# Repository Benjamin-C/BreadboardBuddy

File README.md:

# Breadboard Buddy

An RP2040 microcontroller designed to fit neatly on the end of a breadboard

Important: Some software features listed here are not yet implemented. Run the `help` command to see the commands actually implemented in the current firmware version

# Specs
### Power
| Parameter      |     | Min | Typ | Max | Unit |
|----------------|-----|-----|-----|-----|------|
| Input Voltage  | USB |     | 5   |     | V    |
|                | EXT | 5   | 12  | 30  | V    |
|                | AIN | 0   |     | 3.3 | V    |
|                | GPIO| 0   |     | 3.3 | V    |
| Input Current  | USB |     |     | 0.5 | A    |
|                | EXT |     |     | 2   | A    |
|                | GPIO|     |     | 10  | mA   |
| Output Voltage | 3v3 |     | 3.3 |     | V    |
|                | 3v3A|     | 3.3 |     | V    |
|                | GPIO| 0   |     | 3.3 | V    |
| Output Current | 3v3 | 0.5 |     | 2   | A    |
|                | GPIO|     |     | 10  | mA   |

### System
* Microcontroller: RP2040
* Flash: 2MB

### Peripherals
* 16 GPIO pins capable of input with pull up/down and constant or PWM output.
* 4 analog inputs
* 1 LED connected to GPIO16
* 1 barrel jack switch connected to GPIO17
* 1 button connected to GPIO18

# Setup

## Wiring
Connect the Breadboard Buddy to a breadboard's power rails. Ensure that the positive and negative outputs go to the red and blue sides of each rail. Connect external circuitry to the GPIO or analog pins. If you are doing a lot of analog circuitry, you may with to configure the right rail to be disconnected and manually connect 3v3A there instead. If you are using any voltage higher than 3.3V in your circuit, ensure that it can not reach any of the input pins to the microcontroller.

Connect the USB port of the Breadboard Buddy to your computer, and open and connect your favorite serial monitor.

## Configuration

The right power rail can be configured to output 3v3, EXT, or USB by moving the jumper near the barrel jack. Removing this jumper disconnects that power rail.

Each pin that you want to be an output will have to be explicitly set up as such by using the `mode` command. GPIO pins can be set up as digital inputs or outputs, or PWM outputs. Analog pins can only be set up as analog inputs.

## Firmware
The Breadboard Buddy firmware runs on CircuitPython. To Install it:
1. Download CircuitPython for the Raspberry Pi Pico from https://circuitpython.org/board/raspberry_pi_pico/
2. Connect the Breadboard Buddy to your computer. Disconnect anything else from the Breadboard Buddy.
3. Press and hold the `Reset` button, then press and hold the `Boot` button
4. Release the `Reset` button then release the `Boot` button.
5. The Breadboard buddy should appear as a USB mass storage device named `RPI-RP2`. If this does not happen, try steps 3 and 4 again, waiting longer between actions. If the issue precisest, you have an issue with your hardware.
6. Copy CircuitPython file `adafruit-circuitpython-raspberry_pi_pico-en_US-<version>.uf2` onto the Breadboard Buddy. It should reboot when this is complete.
7. The Breadboard Buddy should now appear as a USB mass storage device named `CIRCUITPY`. If this does not happen, try again from step 3. If the issue precisest, you have an issue with your hardware.
8. Copy `code.py` from `firmware` onto the Breadboard Buddy. The Breadboard Buddy should blink its light several times. You have now installed the Breadboard Buddy firmware.

It is possible to run other software on the Breadboard Buddy either through CircuitPython or by flashing it yourself. This guide will not help you with that.

# Usage

The Breadboard Buddy is interfaced with by sending commands over serial and reading their response.

## Command Types
There are two forms of commands, questions and instructions.
### Instructions
An instruction tells the Breadboard Buddy to do something. This could be to change a configuration field, or set an output value. Most instructions will take the form `<instruction> <field> <value>`. If no value is provided, the command will be assumed to be a question.
### Questions
Questions are asked in the form `<question>[?] <field>`. While the question mark is not required, it is encouraged since any command given with a question mark will be interpreted as a question, even if values are given (in which case they will be ignored).

## Pins
### Pin Fields
For commands that take a pin as a field, there are several ways the pin can be specified. 
#### By number
Pins can be specified by number. Digital pins are 0-15. Analog pins are  ain0-ain4. Example: `5`, `12`, `3`, `ain2`
#### By Name
Pins can also be set up to be identified by a name. Names can be used in place of numbers. Names must be unique for each pin, and each pin can only have 1 alias. Names may contain letters and numbers, but no dashes, spaces, or other characters. Names must start with a letter. Names are not case sensitive, but the given case is stored. Example: `LED`, `BitClk`, `Q`, `Addr2`
#### By range
Pins can be specified by a range. Ranges are specified by a start pin then a dash then the end pin. Ranges are inclusive. The range will be evaluated in the order given. If names are used, they will be converted to pin numbers before the range is calculated. Names and numbers can be mixed. You may not mix analog and digital pins in a range. Example: `0-7`, `ADDR0-ADDR4`, `ain0-ain3`
#### By list
Pins can be specified by a list. Lists are comma separated. The command will execute on each pin in the order they are specified. Names and numbers can be mixed. Example: `1,2,8,4`, `ADDR0,ADDR1,ADDR2`

### Pin States

#### Digital
Digital pins can be either high, low, or a PWM value. When specifying the state of a pin, you can use

* `H`, `HIGH`, `1`, `ON` for high output
* `L`, `LOW`, `0`, `OFF` for low output
* Numbers from 0.000 to 1.000 (only if the pin is configured as PWM)

Note that `ON` and `OFF` should be avoided if you are using active low logic to avoid confusion since they do not reverse for active low signals.

#### Analog
Analog pins will return the voltage on that pin in the form `#.###`. Analog pins can not be set to values.

## Commands

Some commands have a short form and a long form. The short form is the part of the long form shown in CAPS. Either form is acceptable. No part of a command is case sensitive. Multiple fields are separated by spaces. Commands listed with a ? are read only. 

All commands are in the form `<command>[?] <pin(s)> [field(s)]`

| Command | Allowed Fields                         | Action
|---------|----------------------------------------|- 
| Mode    | OUTPUT,INPUT,PULLUP,PULLDOWN,PWM       | Sets/gets the mode of a digital pin
| Name    | Pin name                               | Sets/gets the name of a digital or analog pin
| Digital | Digital pin states                     | Sets/gets value of a digital pin
| Analog? | none                                   | Gets the value of an analog pin
| Read?   | none                                   | Reads the value on any pin
| Bin     | `0`,`1`                                | Sets/gets the value of pins in binary

### Mode
The mode command sets up digital pins. `OUTPUT` sets the pin up as an output and sets the pin's value to low. `INPUT`,`PULLUP`, and `PULLDOWN` set up the pin as an input with the pull if specified. `PWM` sets up the pin as a PWM output pin. If queried, returns the configuration of the pin.

### Name
Handles aliases for pins. The first field is either `D` or `A` to specify if you are using a digital or an analog pin. The second field is the new name for that pin. Names may only contain letters and numbers, and must contain at least one letter. If the pin is specified by name, the pin will be renamed. If queried by number, the name of that pin is returned. If queried by name, the number of that pin is returned.

### Digital
The digital command interacts with digital pins. The field is the value to set. Setting a PWM pin to high or low will result in 100% or 0% duty cycle respectively. Attempting to set input pins has no effect. Querying output pins returns their set value. Querying input pins returns the value read from that pin. The result of the query will be `H`, `L`, or `0.###`

### Analog
Queries analog pins. The Analog command is always assumed to be a query. The result of the query will be `0.###`

### Read
Reads the value of one or more pins. You can mix analog and digital pins. The Read command is always assumed to be a query. The result of the query will be `H`, `L`, or `0.###`

### Binary
Gets the digital value of pins. The result will be `0` or `1`. If an analog pin is specified, the output will be `0` if the voltage is less than half, `1` otherwise. This command can also be used to set the value of digital pins; in this case it will be treated as an alias of the Digital command.

# The Power System

## Power Input

The Breadboard Buddy can be powered from USB, an external power supply, or both.

### USB
You can power the board using the USB connector you use to communicate with it. The USB port does not support USB-PD. The USB port is protected by a 500mA polyfuse as well as a diode allowing safe connection of both power sources simultaneously.
* 500mA total limit form the USB port
* 500mA 3v3 limit

### EXT
You can also power the board form an external power supply with a 5.5x2.1mm center positive barrel jack. You can supply any voltage from 5V to 30V. This jack is protected by a 2A polyfuse and a diode.
* 2A total limit from the barrel jack
* 2A limit 3v3 limit

## Power Output
The left power rail is always powered from 3v3. The right power rail can be configured to be powered from 3v3, EXT, or USB, or it can be left unpowered. This allows you to provide your own power source to this rail. This rail can be set to USB even if EXT is present.

## Power Domains

Termanology:
* A "rail" is a physical power distribution system found on the side of a breadboard.
* A "domain" is a power net on the PCB. Domains can be connected to rails.

The Breadboard Buddy has 5 power domains summarized in this table and described in more detail below.

| Domain     | Description    | Source                | Voltage | Current | Notes |
|------------|----------------|-----------------------|---------|---------|-------|
| 3v3 (3v3D) | Digital supply | VBUS                  | 3.3V    | Max 2A  |       |
| EXT        | External input | 5.5x2.1mm Barrel jack | 5-30V   | Max 2A polyfused |       |
| 3v3A       | Analog supply  | VBUS                  | 3.3V    | 150mA   | For use only in analog circuits 
| USB        | USB input      | USB-C port            | 5V      | 500mA polyfused | Limits 3v3 to 500mA if used
| VBUS       | System power   | Higher of EXT or USB  | 5-30V   | 2A or 500mA | Not accessible externally

### 3v3 (aka 3v3D)
This is the main 3.3V power domain. It is powered by a switching voltage regulator from VBUS. It is used for the digital parts of the board, as well as the 3.3V output on the left power rails, and optionally the right power rails. When powered from EXT, it can supply up to 2A, although this may be limited by the board's power source. When powered from USB, it can supply up to 500mA. This domain should be used for all external digital circuitry.

### EXT
This is the external power source provided through the barrel jack. It is used to supply the voltage regulators if it is present. It can also be sent to the right power rails if desired. It has a total capacity of 2A which may be limited by the external power supply, and it is shared between VBUS and the breadboard power rails.

### 3v3A
This is the analog supply. It is powered by a linear voltage regulator. It is used for the analog parts of the RP2040, and is made available for external analog circuitry on the analog pin header. This domain should be used for all external analog circuitry to reduce power supply noise.

### USB
This is the USB power input. It is used to supply the voltage regulators if EXT is not present. It can also be sent to the right power rails if desired. It has a total capacity of 500mA which is shared between the rails and VBUS if EXT is not present.

### VBUS
This is the power domain that powers the voltage regulators. It is powered by EXT if it is present, or USB. It is not accessible externally.

# Credits
* The center positive symbol came from [Wikipedia](https://en.m.wikipedia.org/wiki/File:Polarity_marking_center_positive.svg). The image is in the public domain.
* The firmware is built on top of [CircuitPython](https://circuitpython.org/)

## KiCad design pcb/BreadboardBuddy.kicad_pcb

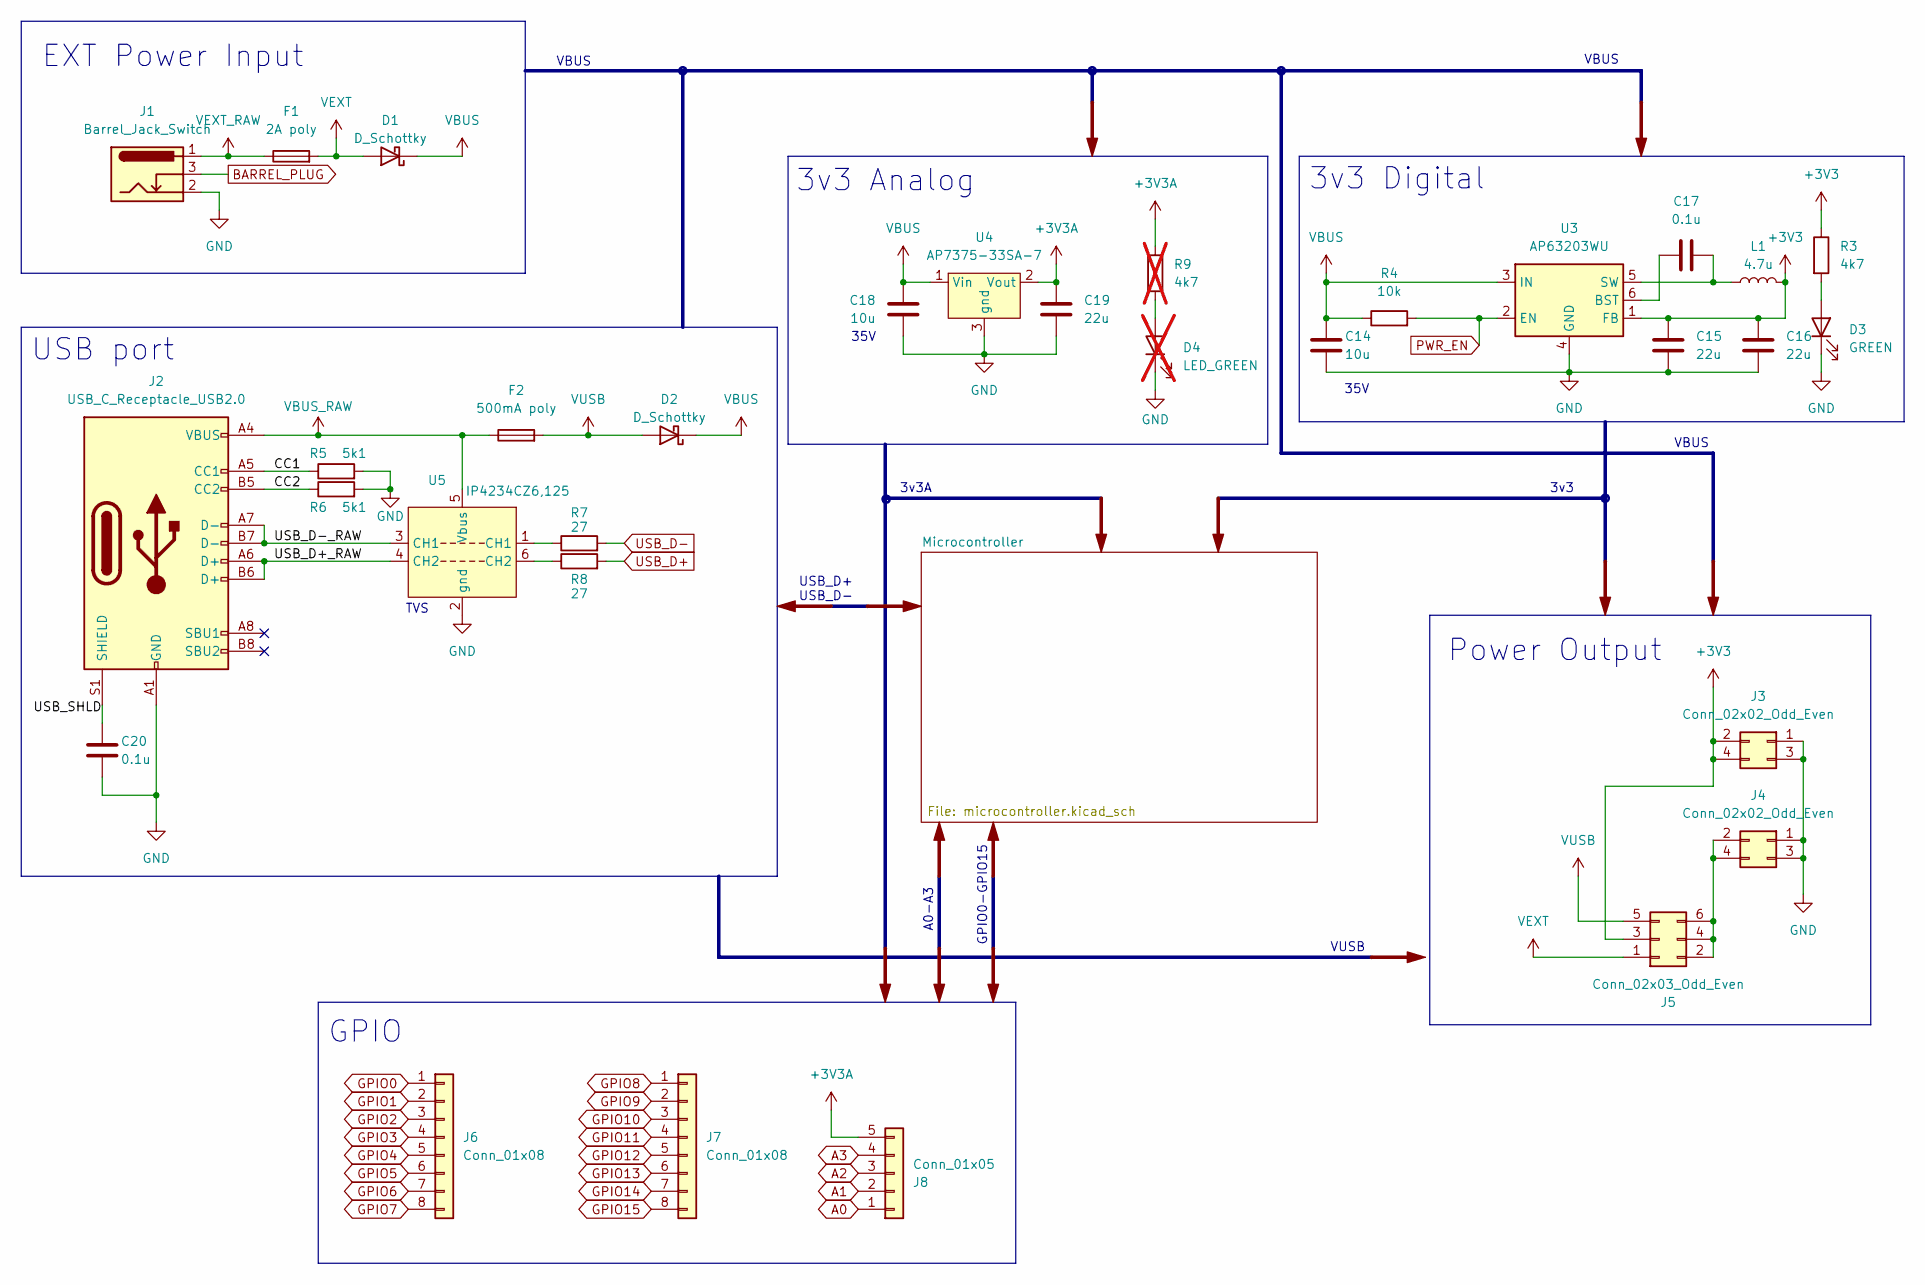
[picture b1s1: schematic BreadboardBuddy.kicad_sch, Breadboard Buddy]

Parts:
C14, C18: 10u; C_0603_1608Metric; MPN GRM188R6YA106MA73D
C15, C16, C19: 22u; C_0603_1608Metric; MPN GRM188R60J226MEA0D
C17, C20: 0.1u; C_0603_1608Metric; MPN CL10B104KO8NFNC
D1, D2: D_Schottky; D_1206_3216Metric; MPN SD1206S040S2R0
D3: GREEN; LED_0603_1608Metric; MPN B1911NG--20D000214U1930
D4: LED_GREEN; LED_0603_1608Metric; MPN B1911PG--20D000514U1930; not fitted
F1: 2A poly; Fuse_1206_3216Metric; MPN 1210L110/16WR
F2: 500mA poly; Fuse_1206_3216Metric; MPN 1206L025YR
J1: Barrel_Jack_Switch; BarrelJack_Wuerth_6941xx301002; MPN PJ-002A
J2: USB_C_Receptacle_USB2.0; USB_C_Receptacle_Palconn_UTC16-G; MPN 2073-USB4105-GF-ACT-ND
J3, J4: Conn_02x02_Odd_Even; PinHeader_2x02_P2.54mm_Vertical; MPN CONN HEADER VERT 4POS 2.54MM
J5: Conn_02x03_Odd_Even; PinHeader_2x03_P2.54mm_Vertical; MPN PH2-06-UA
J6, J7: Conn_01x08; PinHeader_1x08_P2.54mm_Vertical; MPN PH1-08-UA
J8: Conn_01x05; PinHeader_1x05_P2.54mm_Vertical; MPN PH1-05-UA
L1: 4.7u; L_1210_3225Metric; MPN SRP3212-4R7M
R3: 4k7; R_0603_1608Metric; MPN RMCF0603FT470R
R4: 10k; R_0603_1608Metric; MPN RMCF0603FT10K0
R5, R6: 5k1; R_0603_1608Metric; MPN RMCF0603FT5K10
R7, R8: 27; R_0603_1608Metric; MPN CR0603-FX-27R0ELF
R9: 4k7; R_0603_1608Metric; MPN RMCF0603FT470R; not fitted
U3: AP63203WU; TSOT-23-6; MPN AP63203WU-7
U4: AP7375-33SA-7; SOT-23; MPN AP7375-33SA-7
U5: IP4234CZ6,125; TSOP-6_1.65x3.05mm_P0.95mm; MPN IP4234CZ6,125

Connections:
+3V3: C15.1, C16.1, J3.2, J3.4, J5.3, L1.2, R3.1, U3.1 (FB); also elsewhere on the board
+3V3A: C19.1, J8.5, R9.1, U4.2 (Vout); also elsewhere on the board
/CC1: J2.A5 (CC1), R5.1
/CC2: J2.B5 (CC2), R6.1
/USB_D+_RAW: J2.A6 (D+), J2.B6 (D+), U5.4 (CH2)
/USB_D-_RAW: J2.A7 (D-), J2.B7 (D-), U5.3 (CH1)
/USB_SHLD: C20.1, J2.S1 (SHIELD)
A0: J8.1; also elsewhere on the board
A1: J8.2; also elsewhere on the board
A2: J8.3; also elsewhere on the board
A3: J8.4; also elsewhere on the board
BARREL_PLUG: J1.3; also elsewhere on the board
GND: C14.2, C15.2, C16.2, C18.2, C19.2, C20.2, D3.1 (K), D4.1 (K), J1.2, J2.A1 (GND), J2.A12 (GND), J2.B1 (GND), J2.B12 (GND), J3.1, J3.3, J4.1, J4.3, R5.2, R6.2, U3.4 (GND), U4.3 (gnd), U5.2 (gnd); also elsewhere on the board
GPIO0: J6.1; also elsewhere on the board
GPIO1: J6.2; also elsewhere on the board
GPIO2: J6.3; also elsewhere on the board
GPIO3: J6.4; also elsewhere on the board
GPIO4: J6.5; also elsewhere on the board
GPIO5: J6.6; also elsewhere on the board
GPIO6: J6.7; also elsewhere on the board
GPIO7: J6.8; also elsewhere on the board
GPIO8: J7.1; also elsewhere on the board
GPIO9: J7.2; also elsewhere on the board
GPIO10: J7.3; also elsewhere on the board
GPIO11: J7.4; also elsewhere on the board
GPIO12: J7.5; also elsewhere on the board
GPIO13: J7.6; also elsewhere on the board
GPIO14: J7.7; also elsewhere on the board
GPIO15: J7.8; also elsewhere on the board
unnamed: D3.2 (A), R3.2
unnamed: D4.2 (A), R9.2
unnamed: J4.2, J4.4, J5.2, J5.4, J5.6
unnamed: R7.1, U5.1 (CH1)
unnamed: R8.1, U5.6 (CH2)
unnamed: C17.1, U3.6 (BST)
unnamed: C17.2, L1.1, U3.5 (SW)
PWR_EN: R4.2, U3.2 (EN)
USB_D+: R8.2; also elsewhere on the board
USB_D-: R7.2; also elsewhere on the board
VBUS: C14.1, C18.1, D1.1 (K), D2.1 (K), R4.1, U3.3 (IN), U4.1 (Vin)
VBUS_RAW: F2.1, J2.A4 (VBUS), J2.A9 (VBUS), J2.B4 (VBUS), J2.B9 (VBUS), U5.5 (Vbus)
VEXT: D1.2 (A), F1.2, J5.1
VEXT_RAW: F1.1, J1.1
VUSB: D2.2 (A), F2.2, J5.5

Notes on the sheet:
35V
VBUS
USB port
GPIO0-GPIO15
3v3 Analog
3v3 Digital
Power Output
USB_D+ USB_D-
3v3A
TVS
GPIO
EXT Power Input
A0-A3
3v3
VUSB

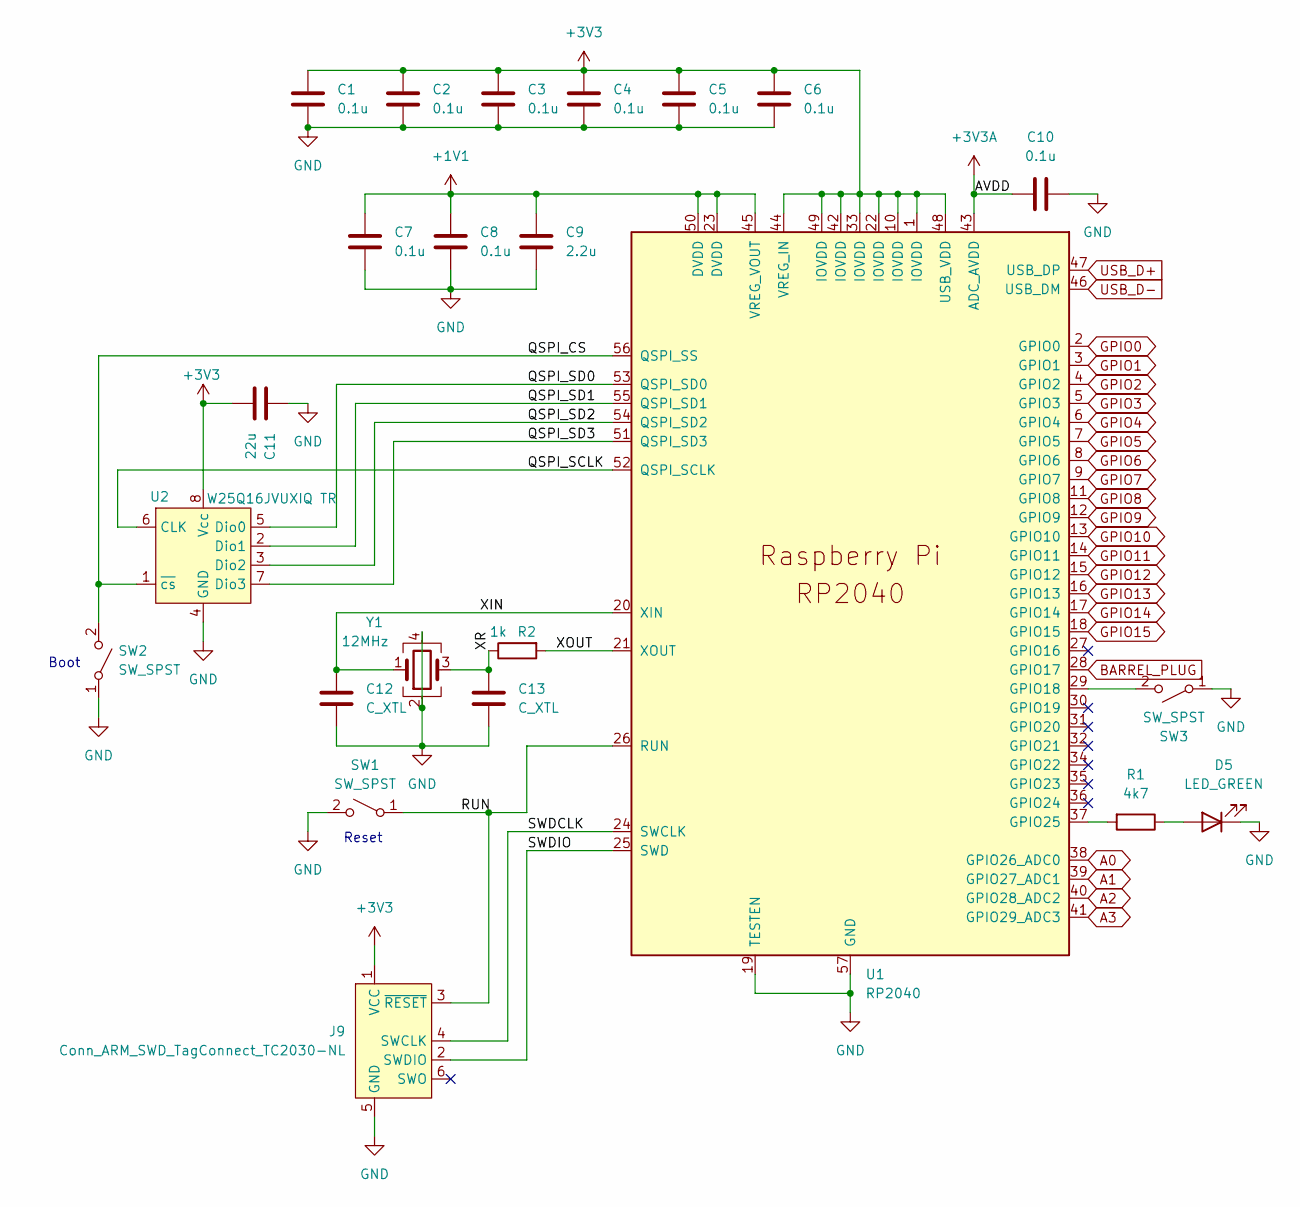
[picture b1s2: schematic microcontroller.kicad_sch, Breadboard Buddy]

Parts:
C1, C2, C3, C4, C5, C6, C7, C8, C10: 0.1u; C_0603_1608Metric; MPN CL10B104KO8NFNC
C9: 2.2u; C_0603_1608Metric; MPN CL10A225KP8NNNC
C11: 22u; C_0603_1608Metric; MPN GRM188R60J226MEA0D
C12, C13: C_XTL; C_0603_1608Metric; MPN 0603N150J500CT
D5: LED_GREEN; LED_0603_1608Metric; MPN B1911PG--20D000514U1930
J9: Conn_ARM_SWD_TagConnect_TC2030-NL; Tag-Connect_TC2030-IDC-NL_2x03_P1.27mm_Vertical
R1: 4k7; R_0603_1608Metric; MPN RMCF0603FT470R
R2: 1k; R_0603_1608Metric; MPN RMCF0603FT1K00
SW1, SW2, SW3: SW_SPST; SW_SPST_3.3x3.1; MPN LS38J2F-T
U1: RP2040; QFN-56-1EP_7x7mm_P0.4mm_EP3.2x3.2mm_ThermalVias; MPN SC0914(13)
U2: W25Q16JVUXIQ TR; 8-UFDFN; MPN W25Q16JVUXIQ TR
Y1: 12MHz; Crystal_SMD_3225-4Pin_3.2x2.5mm; MPN RH100-12.000-12-1010-X-TR-NS2

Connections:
+1V1: C7.1, C8.1, C9.1, U1.23 (DVDD), U1.45 (VREG_VOUT), U1.50 (DVDD)
+3V3: C1.1, C2.1, C3.1, C4.1, C5.1, C6.1, C11.2, J9.1 (VCC), U1.1 (IOVDD), U1.10 (IOVDD), U1.22 (IOVDD), U1.33 (IOVDD), U1.42 (IOVDD), U1.44 (VREG_IN), U1.48 (USB_VDD), U1.49 (IOVDD), U2.8 (Vcc); also elsewhere on the board
+3V3A: C10.1, U1.43 (ADC_AVDD); also elsewhere on the board
/Microcontroller/QSPI_CS: SW2.2 (B), U1.56 (QSPI_SS), U2.1 (~cs)
/Microcontroller/QSPI_SCLK: U1.52 (QSPI_SCLK), U2.6 (CLK)
/Microcontroller/QSPI_SD0: U1.53 (QSPI_SD0), U2.5 (Dio0)
/Microcontroller/QSPI_SD1: U1.55 (QSPI_SD1), U2.2 (Dio1)
/Microcontroller/QSPI_SD2: U1.54 (QSPI_SD2), U2.3 (Dio2)
/Microcontroller/QSPI_SD3: U1.51 (QSPI_SD3), U2.7 (Dio3)
/Microcontroller/RUN: J9.3 (~RESET), SW1.1 (A), U1.26 (RUN)
/Microcontroller/SWDCLK: J9.4 (SWCLK), U1.24 (SWCLK)
/Microcontroller/SWDIO: J9.2 (SWDIO), U1.25 (SWD)
/Microcontroller/XIN: C12.1, U1.20 (XIN), Y1.1
/Microcontroller/XOUT: R2.2, U1.21 (XOUT)
/Microcontroller/XR: C13.1, R2.1, Y1.3
A0: U1.38 (GPIO26_ADC0); also elsewhere on the board
A1: U1.39 (GPIO27_ADC1); also elsewhere on the board
A2: U1.40 (GPIO28_ADC2); also elsewhere on the board
A3: U1.41 (GPIO29_ADC3); also elsewhere on the board
BARREL_PLUG: U1.28 (GPIO17); also elsewhere on the board
GND: C1.2, C2.2, C3.2, C4.2, C5.2, C6.2, C7.2, C8.2, C9.2, C10.2, C11.1, C12.2, C13.2, D5.1 (K), J9.5 (GND), SW1.2 (B), SW2.1 (A), SW3.1 (A), U1.19 (TESTEN), U1.57 (GND), U2.4 (GND), Y1.2, Y1.4; also elsewhere on the board
GPIO0: U1.2 (GPIO0); also elsewhere on the board
GPIO1: U1.3 (GPIO1); also elsewhere on the board
GPIO2: U1.4 (GPIO2); also elsewhere on the board
GPIO3: U1.5 (GPIO3); also elsewhere on the board
GPIO4: U1.6 (GPIO4); also elsewhere on the board
GPIO5: U1.7 (GPIO5); also elsewhere on the board
GPIO6: U1.8 (GPIO6); also elsewhere on the board
GPIO7: U1.9 (GPIO7); also elsewhere on the board
GPIO8: U1.11 (GPIO8); also elsewhere on the board
GPIO9: U1.12 (GPIO9); also elsewhere on the board
GPIO10: U1.13 (GPIO10); also elsewhere on the board
GPIO11: U1.14 (GPIO11); also elsewhere on the board
GPIO12: U1.15 (GPIO12); also elsewhere on the board
GPIO13: U1.16 (GPIO13); also elsewhere on the board
GPIO14: U1.17 (GPIO14); also elsewhere on the board
GPIO15: U1.18 (GPIO15); also elsewhere on the board
unnamed: D5.2 (A), R1.1
unnamed: SW3.2 (B), U1.29 (GPIO18)
unnamed: R1.2, U1.37 (GPIO25)
USB_D+: U1.47 (USB_DP); also elsewhere on the board
USB_D-: U1.46 (USB_DM); also elsewhere on the board

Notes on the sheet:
Reset
Boot

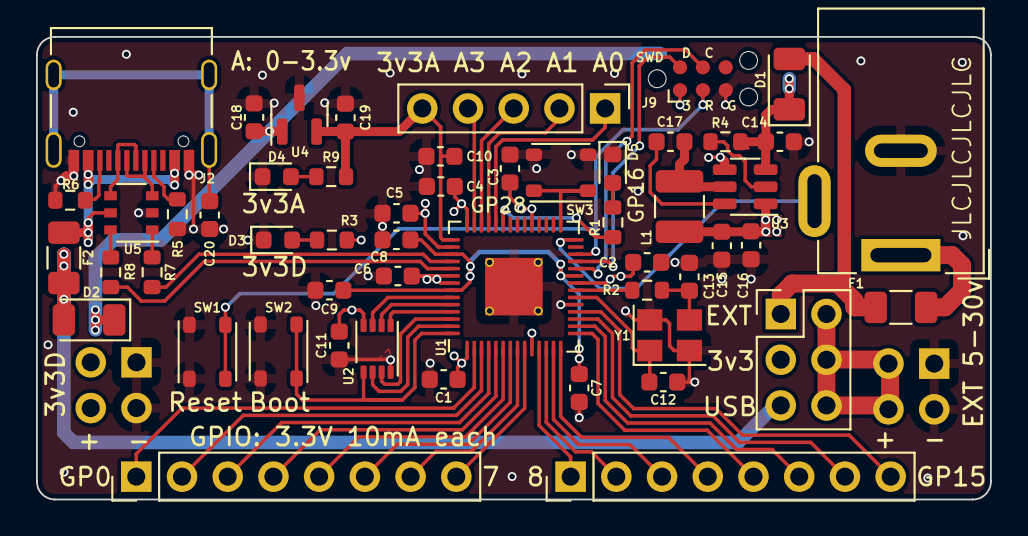
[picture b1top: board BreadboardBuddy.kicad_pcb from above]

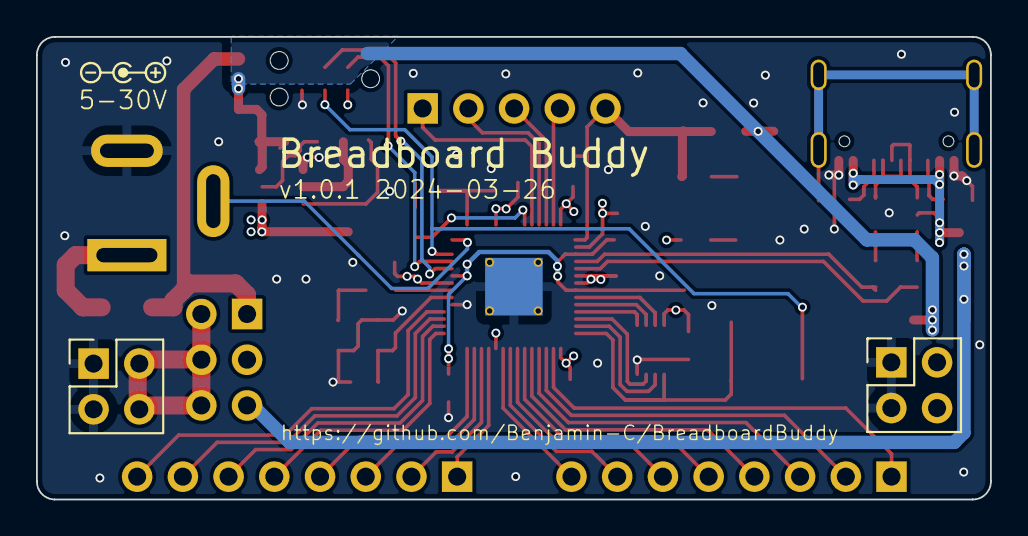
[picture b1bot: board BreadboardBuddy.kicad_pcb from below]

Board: 4 copper layers, 53.0 x 25.7 mm, 55 parts (2 on the bottom side), 60 nets.

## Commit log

2024-03-10 Created PCB
2024-03-10 Added readme
2024-03-10 Added docs
2024-03-10 Removed locks from git
2024-03-11 Added command and power docs
2024-03-11 Prepped for DR
2024-03-12 Prepared for fab
2024-04-12 Added firmware
2024-04-21 Cleaned up repo
2024-04-21 Fixed board USB issue
2024-04-21 Improved flash footprint
2024-04-21 Cleaned up
2026-05-13 Minor firmware fix
2026-05-13 Clarified firmware state
